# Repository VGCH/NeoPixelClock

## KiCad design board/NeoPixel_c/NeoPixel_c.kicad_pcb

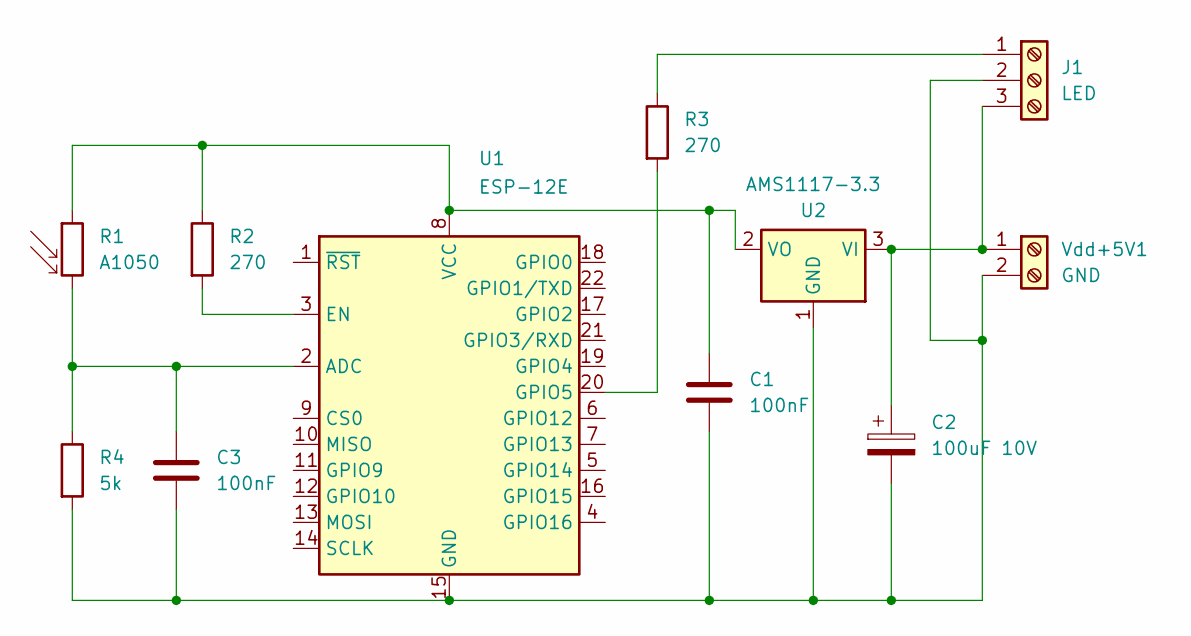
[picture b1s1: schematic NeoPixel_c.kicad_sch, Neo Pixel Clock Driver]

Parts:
C1, C3: 100nF; C_0805_2012Metric
C2: 100uF 10V; CP_Elec_5x5.8
J1: LED; PinHeader_1x03_P1.00mm_Vertical
R1: A1050; R_LDR_D6.4mm_P3.4mm_Vertical
R2, R3: 270; R_0805_2012Metric
R4: 5k; R_0805_2012Metric
U1: ESP-12E
U2: AMS1117-3.3; SOT-223-3_TabPin2
Vdd+5V1: GND; PinHeader_1x02_P1.00mm_Vertical

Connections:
unnamed: J1.1, R3.1
unnamed 1: C1.2, C2.2, C3.2, J1.2, R4.2, U1.15 (GND), U2.1 (GND), Vdd+5V1.2; also elsewhere on the board
unnamed 2: C2.1, J1.3, U2.3 (VI), Vdd+5V1.1; also elsewhere on the board
unnamed: C3.1, R1.2, R4.1, U1.2 (ADC)
unnamed: R2.2, U1.3 (EN)
unnamed: R3.2, U1.20 (GPIO5)
unnamed: C1.1, R1.1, R2.1, U1.8 (VCC), U2.2 (VO)

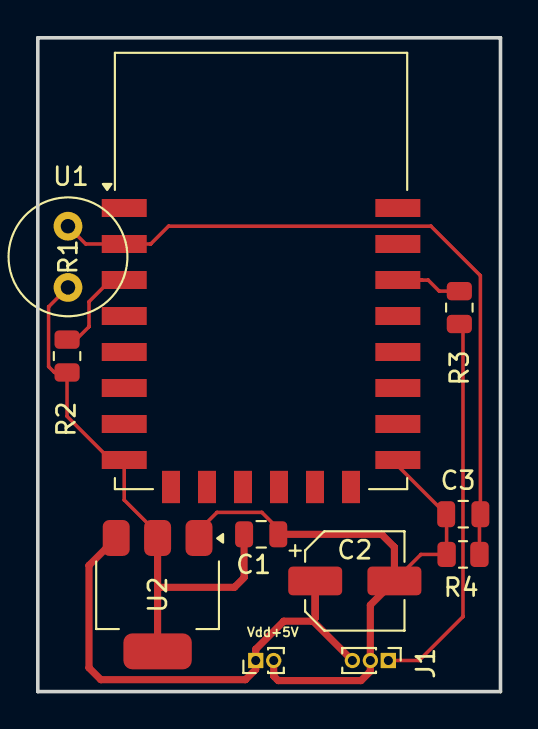
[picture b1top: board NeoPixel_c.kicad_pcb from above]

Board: 2 copper layers, 25.7 x 36.3 mm, 11 parts (0 on the bottom side), 7 nets.

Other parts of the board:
Vdd+5V: GND; PinHeader_1x02_P1.00mm_Vertical

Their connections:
unnamed 1: Vdd+5V.2; also elsewhere on the board
unnamed 2: Vdd+5V.1; also elsewhere on the board

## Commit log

2024-11-08 update commit
